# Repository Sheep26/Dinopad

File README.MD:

## Dinopad
Dinopad, is a small 16 key macropad, which features a diode matrix and a rotary encoder. The PCB is littered with dinosaurs, that's why it's called Dinopad.

## Case

## Schematic

## PCB

## 3D model

## BOM
|"Id"|"Part"|"Designator"|"Footprint"|"Quantity"|"Designation"|
|----|------|------------|-----------|----------|-------------|
|1|"MX-Style switches"|"SW1| SW2| SW3| SW4| SW5| SW6| SW7| SW8| SW9| SW11| SW12| SW13| SW14| SW15| SW16| SW17"|"SW_Cherry_MX_1.00u_PCB"|16|"SW_Push"|
|2|"EC11 Rotary encoder"|"SW10"|"RotaryEncoder_Alps_EC11E-Switch_Vertical_H20mm_CircularMountingHoles"|1|"RotaryEncoder_Switch"|
|3|"XIAO RP2040"|"U1"|"XIAO-Generic-Hybrid-14P-2.54-21X17.8MM"|1|"MOUDLE-SEEEDUINO-XIAO"|
|4|"Blank DSA keycaps"|||16||
|5|"Through-hole 1N4148 Diodes"|"D1| D2| D3| D4| D5| D6| D7| D8| D9| D10| D11| D12| D13| D14| D15| D16"|"D_DO-35_SOD27_P7.62mm_Horizontal"|17|"D"|
|6|"4x M3x16 Bolt"|||4||
|7|"M3 Heatset"|||4||

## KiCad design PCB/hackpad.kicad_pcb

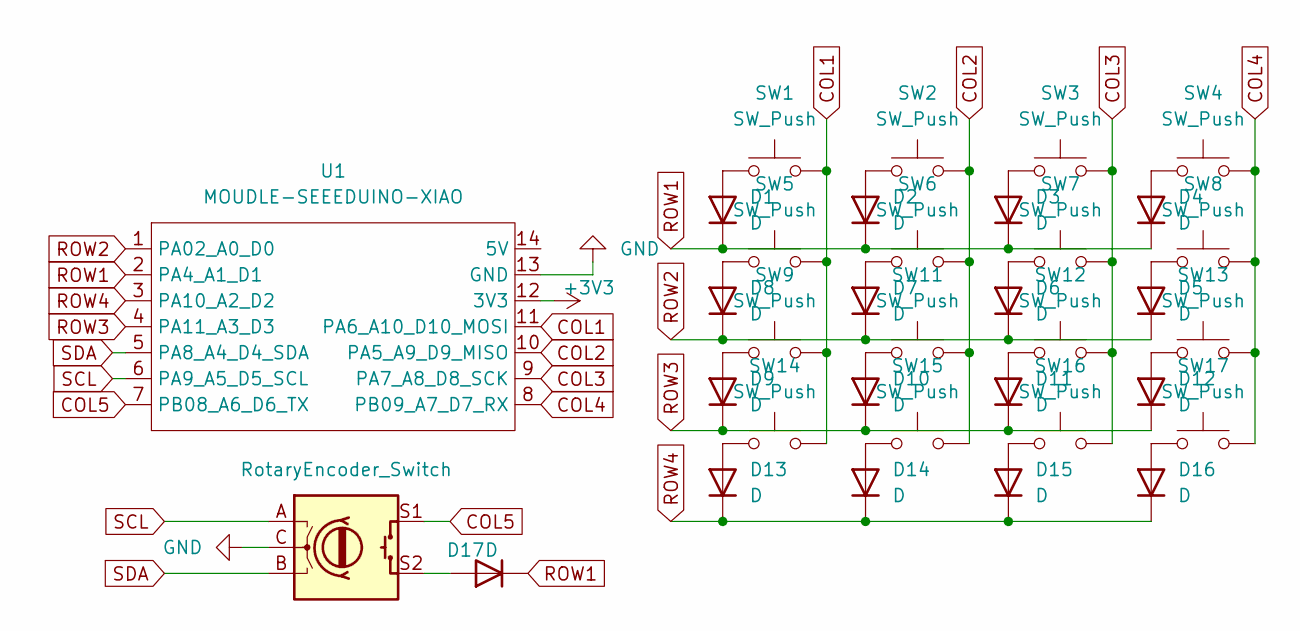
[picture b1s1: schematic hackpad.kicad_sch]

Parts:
D1, D2, D3, D4, D5, D6, D7, D8, D9, D10, D11, D12, D13, D14, D15, D16, D17: D; D_DO-35_SOD27_P7.62mm_Horizontal
SW1, SW2, SW3, SW4, SW5, SW6, SW7, SW8, SW9, SW11, SW12, SW13, SW14, SW15, SW16, SW17: SW_Push; SW_Cherry_MX_1.00u_PCB
SW10: RotaryEncoder_Switch; RotaryEncoder_Alps_EC11E-Switch_Vertical_H20mm_CircularMoun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
U1: MOUDLE-SEEEDUINO-XIAO; XIAO-Generic-Hybrid-14P-2.54-21X17.8MM

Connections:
+3V3: U1.12 (3V3)
COL1: SW1.2, SW5.2, SW9.2, SW14.2, U1.11 (PA6_A10_D10_MOSI)
COL2: SW2.2, SW6.2, SW11.2, SW15.2, U1.10 (PA5_A9_D9_MISO)
COL3: SW3.2, SW7.2, SW12.2, SW16.2, U1.9 (PA7_A8_D8_SCK)
COL4: SW4.2, SW8.2, SW13.2, SW17.2, U1.8 (PB09_A7_D7_RX)
COL5: SW10.S1, U1.7 (PB08_A6_D6_TX)
GND: SW10.C, U1.13 (GND)
unnamed: D1.2 (A), SW1.1
unnamed: D2.2 (A), SW2.1
unnamed: D3.2 (A), SW3.1
unnamed: D4.2 (A), SW4.1
unnamed: D5.2 (A), SW8.1
unnamed: D6.2 (A), SW7.1
unnamed: D7.2 (A), SW6.1
unnamed: D8.2 (A), SW5.1
unnamed: D9.2 (A), SW9.1
unnamed: D10.2 (A), SW11.1
unnamed: D11.2 (A), SW12.1
unnamed: D12.2 (A), SW13.1
unnamed: D13.2 (A), SW14.1
unnamed: D14.2 (A), SW15.1
unnamed: D15.2 (A), SW16.1
unnamed: D16.2 (A), SW17.1
unnamed: D17.2 (A), SW10.S2
ROW1: D1.1 (K), D2.1 (K), D3.1 (K), D4.1 (K), D17.1 (K), U1.2 (PA4_A1_D1)
ROW2: D5.1 (K), D6.1 (K), D7.1 (K), D8.1 (K), U1.1 (PA02_A0_D0)
ROW3: D9.1 (K), D10.1 (K), D11.1 (K), D12.1 (K), U1.4 (PA11_A3_D3)
ROW4: D13.1 (K), D14.1 (K), D15.1 (K), D16.1 (K), U1.3 (PA10_A2_D2)
SCL: SW10.A, U1.6 (PA9_A5_D5_SCL)
SDA: SW10.B, U1.5 (PA8_A4_D4_SDA)

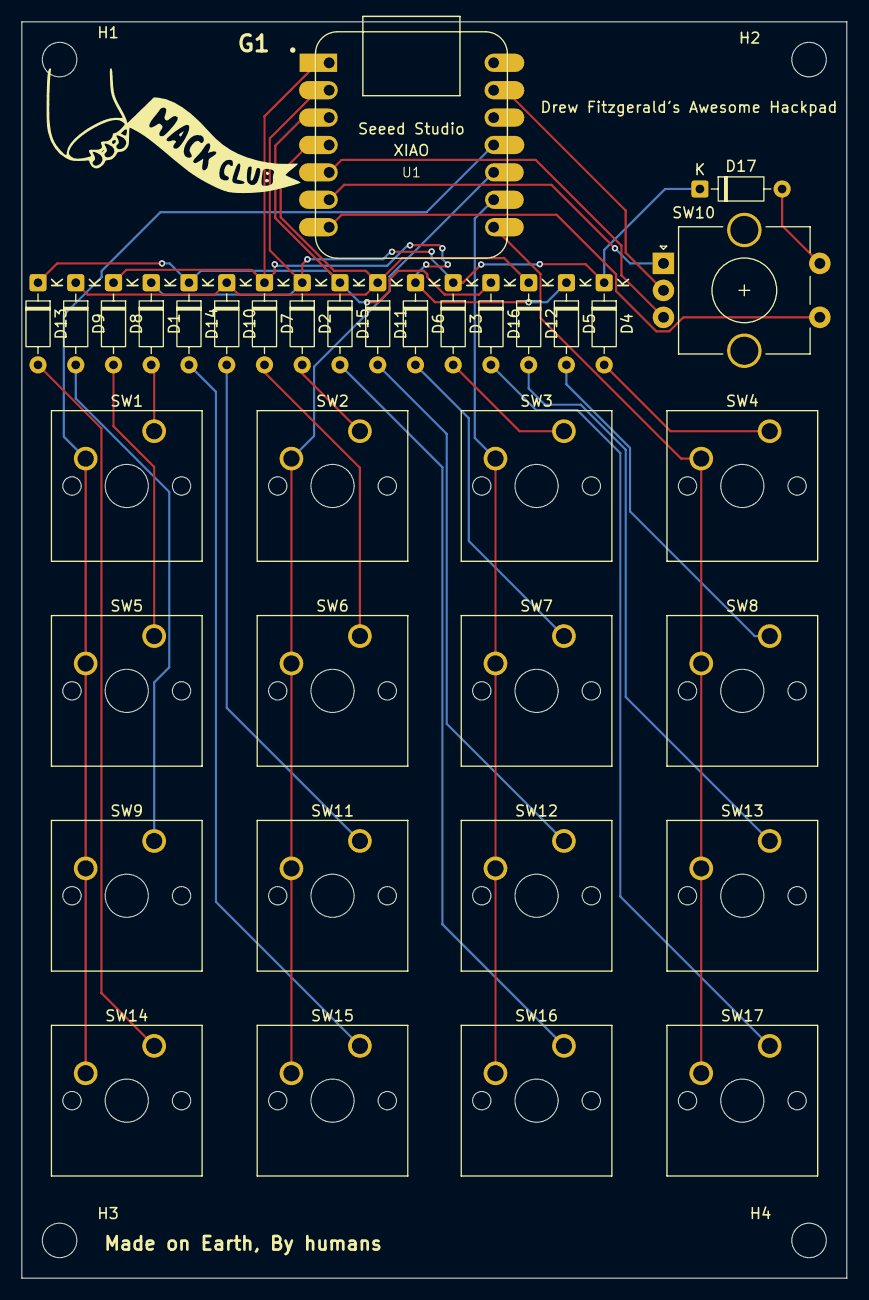
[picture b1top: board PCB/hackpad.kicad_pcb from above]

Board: 2 copper layers, 76.5 x 116.5 mm, 41 parts (1 on the bottom side), 29 nets.

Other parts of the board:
G1, G2: LOGO
H1, H2, H3, H4: MountingHole_3.2mm_M3

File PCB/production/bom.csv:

Designator,Footprint,Quantity,Value,LCSC Part #
"D1, D10, D11, D12, D13, D14, D15, D16, D17, D2, D3, D4, D5, D6, D7, D8, D9",D_DO-35_SOD27_P7.62mm_Horizontal,17,D,
"SW1, SW11, SW12, SW13, SW14, SW15, SW16, SW17, SW2, SW3, SW4, SW5, SW6, SW7, SW8, SW9",SW_Cherry_MX_1.00u_PCB,16,SW_Push,
SW10,RotaryEncoder_Alps_EC11E-Switch_Vertical_H20mm_CircularMountingHoles,1,RotaryEncoder_Switch,
U1,XIAO-Generic-Hybrid-14P-2.54-21X17.8MM,1,MOUDLE-SEEEDUINO-XIAO,

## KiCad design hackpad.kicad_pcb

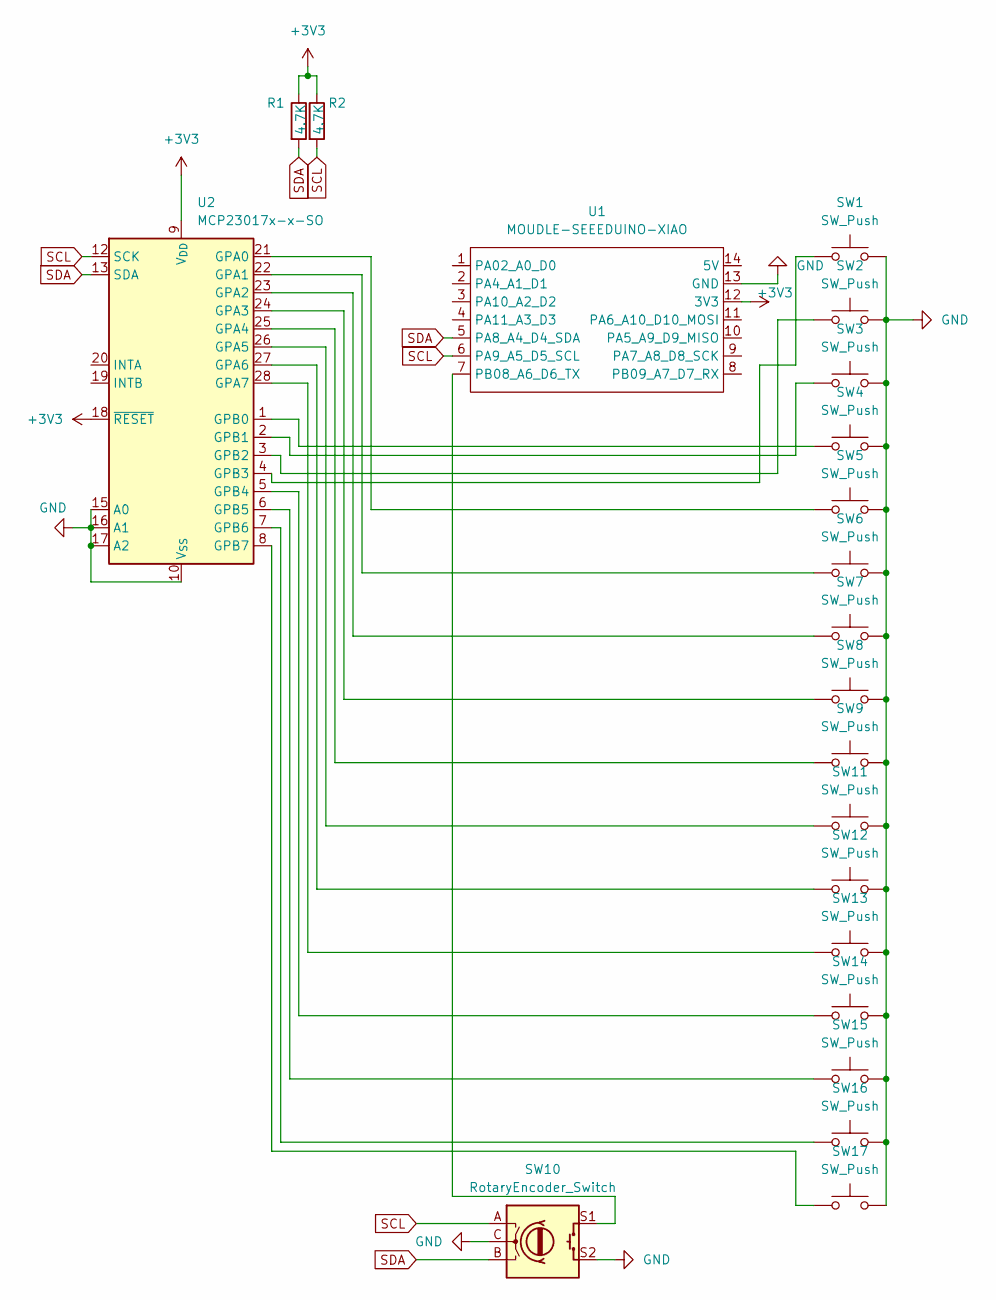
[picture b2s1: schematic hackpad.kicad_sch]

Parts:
R1, R2: 4.7K; R_Axial_DIN0204_L3.6mm_D1.6mm_P7.62mm_Horizontal
SW1, SW2, SW3, SW4, SW5, SW6, SW7, SW8, SW9, SW11, SW12, SW13, SW14, SW15, SW16, SW17: SW_Push; SW_Cherry_MX_1.00u_PCB
SW10: RotaryEncoder_Switch; RotaryEncoder_Alps_EC11E-Switch_Vertical_H20mm_CircularMoun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
U1: MOUDLE-SEEEDUINO-XIAO; XIAO-Generic-Hybrid-14P-2.54-21X17.8MM
U2: MCP23017x-x-SO; SOIC-28W_7.5x17.9mm_P1.27mm

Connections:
+3V3: R1.1, R2.1, U1.12 (3V3), U2.9 (V_{DD}), U2.18 (~RESET)
GND: SW1.2, SW2.2, SW3.2, SW4.2, SW5.2, SW6.2, SW7.2, SW8.2, SW9.2, SW10.C, SW10.S2, SW11.2, SW12.2, SW13.2, SW14.2, SW15.2, SW16.2, SW17.2, U1.13 (GND), U2.10 (V_{SS}), U2.15 (A0), U2.16 (A1), U2.17 (A2)
unnamed: SW10.S1, U1.7 (PB08_A6_D6_TX)
unnamed: SW5.1, U2.21 (GPA0)
unnamed: SW6.1, U2.22 (GPA1)
unnamed: SW7.1, U2.23 (GPA2)
unnamed: SW8.1, U2.24 (GPA3)
unnamed: SW9.1, U2.25 (GPA4)
unnamed: SW11.1, U2.26 (GPA5)
unnamed: SW12.1, U2.27 (GPA6)
unnamed: SW13.1, U2.28 (GPA7)
unnamed: SW4.1, U2.1 (GPB0)
unnamed: SW3.1, U2.2 (GPB1)
unnamed: SW2.1, U2.3 (GPB2)
unnamed: SW1.1, U2.4 (GPB3)
unnamed: SW14.1, U2.5 (GPB4)
unnamed: SW15.1, U2.6 (GPB5)
unnamed: SW16.1, U2.7 (GPB6)
unnamed: SW17.1, U2.8 (GPB7)
SCL: R2.2, SW10.A, U1.6 (PA9_A5_D5_SCL), U2.12 (SCK)
SDA: R1.2, SW10.B, U1.5 (PA8_A4_D4_SDA), U2.13 (SDA)

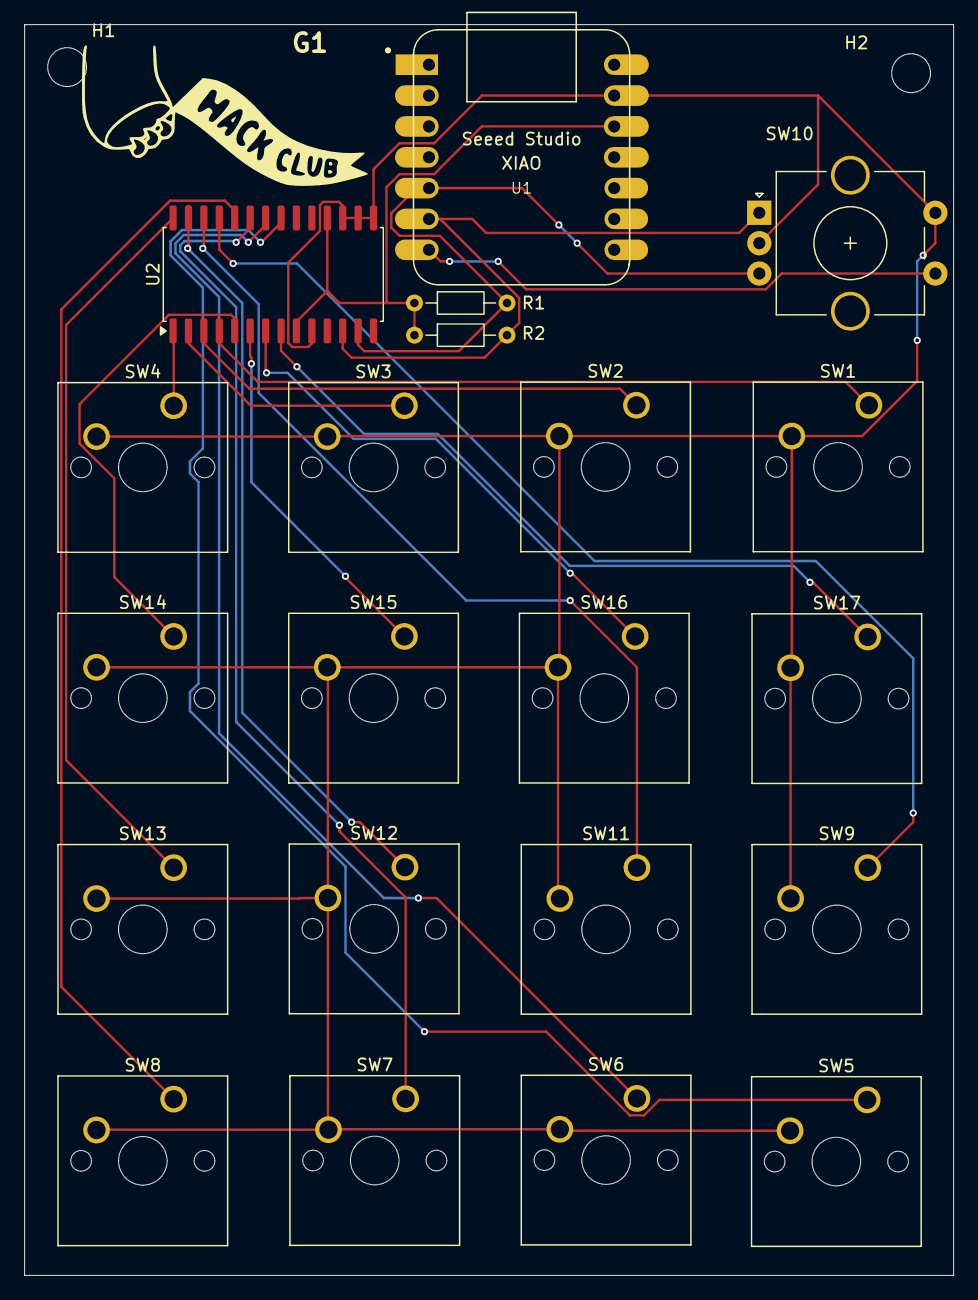
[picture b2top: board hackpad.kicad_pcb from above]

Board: 2 copper layers, 76.5 x 103.0 mm, 25 parts (1 on the bottom side), 21 nets.

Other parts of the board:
G1, G2: LOGO
H1, H2: MountingHole_3.2mm_M3
